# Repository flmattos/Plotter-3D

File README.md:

# Plotter-3D

#Engenharia da Computação

#PUCPR

#3D

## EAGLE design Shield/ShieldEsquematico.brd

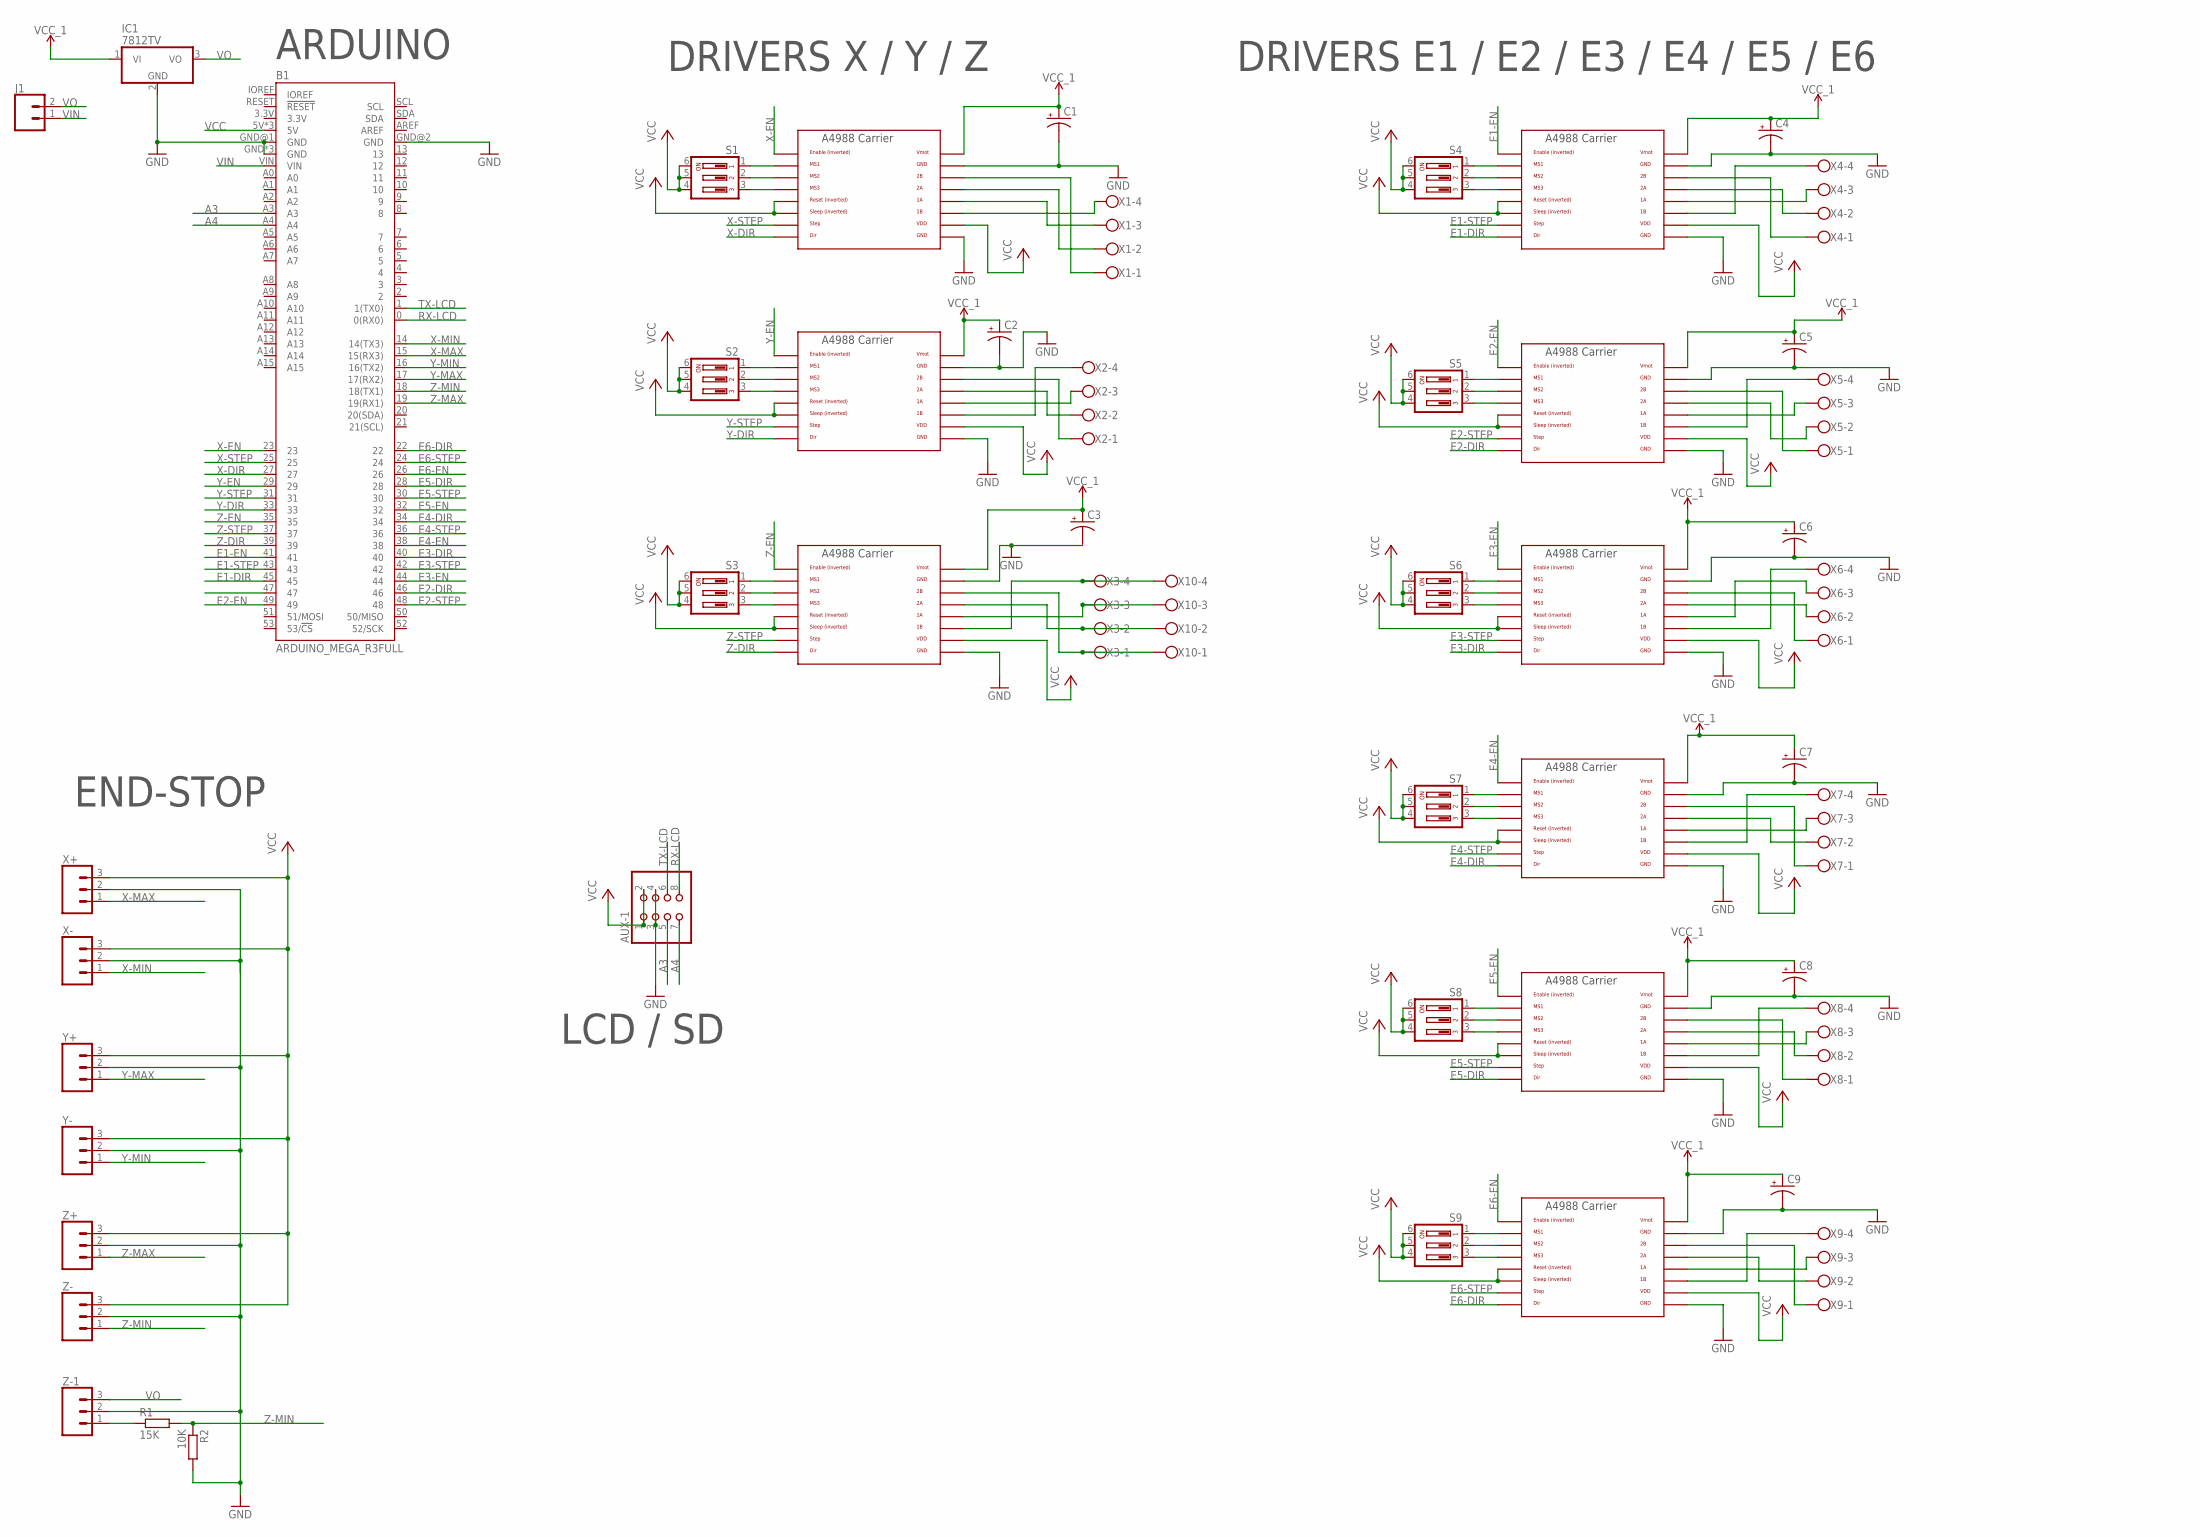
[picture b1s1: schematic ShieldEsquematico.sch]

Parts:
AUX-1: PINHD-2X4; 2X04
B1: ARDUINO_MEGA_R3FULL; ARDUINO_MEGA_NO_SILK
C1, C2, C3, C4, C5, C6, C7, C8, C9: CPOL-USE5-8.5; E5-8,5
IC1: 7812TV; TO220V
J1: CONN_02; 1X02
R1: 15K; 0207/10
R2: 10K; 0207/10
S1, S2, S3, S4, S5, S6, S7, S8, S9: DIP03YL
U$1, U$2, U$3, U$4, U$5, U$6, U$7, U$8, U$9: A4988BREAKOUT
X1, X2, X3, X4, X5, X6, X7, X8, X9, X10: W237-4
X+: CONN_03SCREW_LOCK; SCREWTERMINAL-3.5MM-3_LOCK.007S
X-: CONN_03SCREW_LOCK; SCREWTERMINAL-3.5MM-3_LOCK.007S
Y+: CONN_03SCREW_LOCK; SCREWTERMINAL-3.5MM-3_LOCK.007S
Y-: CONN_03SCREW_LOCK; SCREWTERMINAL-3.5MM-3_LOCK.007S
Z+: CONN_03SCREW_LOCK; SCREWTERMINAL-3.5MM-3_LOCK.007S
Z-, Z-1: CONN_03SCREW_LOCK; SCREWTERMINAL-3.5MM-3_LOCK.007S

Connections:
A3: AUX-1.5, B1.A3
A4: AUX-1.7, B1.A4
E1-DIR: B1.45, U$4.DIR
E1-EN: B1.41, U$4.EN
E1-STEP: B1.43, U$4.STEP
E2-DIR: B1.46, U$5.DIR
E2-EN: B1.49, U$5.EN
E2-STEP: B1.48, U$5.STEP
E3-DIR: B1.40, U$6.DIR
E3-EN: B1.44, U$6.EN
E3-STEP: B1.42, U$6.STEP
E4-DIR: B1.34, U$7.DIR
E4-EN: B1.38, U$7.EN
E4-STEP: B1.36, U$7.STEP
E5-DIR: B1.28, U$8.DIR
E5-EN: B1.32, U$8.EN
E5-STEP: B1.30, U$8.STEP
E6-DIR: B1.22, U$9.DIR
E6-EN: B1.26, U$9.EN
E6-STEP: B1.24, U$9.STEP
GND: AUX-1.3, AUX-1.4, B1.GND, B1.GND@1 (GND), B1.GND@2 (GND), B1.GND@3 (GND), B1.GND@4 (GND), C1.-, C2.-, C3.-, C4.-, C5.-, C6.-, C7.-, C8.-, C9.-, IC1.2 (GND), R2.2, U$1.GND, U$1.GND@0 (GND), U$2.GND, U$2.GND@0 (GND), U$3.GND, U$3.GND@0 (GND), U$4.GND, U$4.GND@0 (GND), U$5.GND, U$5.GND@0 (GND), U$6.GND, U$6.GND@0 (GND), U$7.GND, U$7.GND@0 (GND), U$8.GND, U$8.GND@0 (GND), U$9.GND, U$9.GND@0 (GND), X+.2, X-.2, Y+.2, Y-.2, Z+.2, Z-.2, Z-1.2
unnamed: S1.1, U$1.MS1
unnamed: S1.2, U$1.MS2
unnamed: S1.3, U$1.MS3
unnamed: U$1.1B, X1.4
unnamed: U$1.1A, X1.3
unnamed: U$1.2A, X1.2
unnamed: U$1.2B, X1.1
unnamed: S2.1, U$2.MS1
unnamed: S2.2, U$2.MS2
unnamed: S2.3, U$2.MS3
unnamed: U$2.1B, X2.4
unnamed: U$3.2B, X3.1, X10.1
unnamed: U$2.2A, X2.2
unnamed: U$2.2B, X2.1
unnamed: S3.1, U$3.MS1
unnamed: S3.2, U$3.MS2
unnamed: S3.3, U$3.MS3
unnamed: U$3.2A, X3.2, X10.2
unnamed: U$3.1A, X3.3, X10.3
unnamed: U$3.1B, X3.4, X10.4
unnamed: U$4.2B, X4.1
unnamed: S4.1, U$4.MS1
unnamed: S4.2, U$4.MS2
unnamed: S4.3, U$4.MS3
unnamed: U$4.2A, X4.2
unnamed: U$4.1A, X4.3
unnamed: U$4.1B, X4.4
unnamed: U$6.1A, X6.3
unnamed: S5.1, U$5.MS1
unnamed: S5.2, U$5.MS2
unnamed: S5.3, U$5.MS3
unnamed: U$5.2B, X5.1
unnamed: U$5.2A, X5.2
unnamed: U$5.1A, X5.3
unnamed: U$5.1B, X5.4
unnamed: S6.1, U$6.MS1
unnamed: S6.2, U$6.MS2
unnamed: S6.3, U$6.MS3
unnamed: U$6.1B, X6.4
unnamed: U$7.2A, X7.2
unnamed: U$6.2A, X6.2
unnamed: U$6.2B, X6.1
unnamed: S7.1, U$7.MS1
unnamed: S7.2, U$7.MS2
unnamed: S7.3, U$7.MS3
unnamed: U$7.1A, X7.3
unnamed: U$7.1B, X7.4
unnamed: U$9.2B, X9.1
unnamed: U$7.2B, X7.1
unnamed: S8.1, U$8.MS1
unnamed: S8.2, U$8.MS2
unnamed: S8.3, U$8.MS3
unnamed: U$8.2B, X8.1
unnamed: U$8.2A, X8.2
unnamed: U$8.1A, X8.3
unnamed: U$8.1B, X8.4
unnamed: S9.1, U$9.MS1
unnamed: S9.2, U$9.MS2
unnamed: S9.3, U$9.MS3
unnamed: U$9.2A, X9.2
unnamed: U$9.1A, X9.3
unnamed: U$9.1B, X9.4
unnamed: R1.1, Z-1.1
unnamed: U$2.1A, X2.3
RX-LCD: AUX-1.8, B1.0 (0(RX0))
TX-LCD: AUX-1.6, B1.1 (1(TX0))
VCC: AUX-1.1, AUX-1.2, B1.5V, B1.5V@1 (5V), B1.5V@2 (5V), S1.4, S1.5, S1.6, S2.4, S2.5, S2.6, S3.4, S3.5, S3.6, S4.4, S4.5, S4.6, S5.4, S5.5, S5.6, S6.4, S6.5, S6.6, S7.4, S7.5, S7.6, S8.4, S8.5, S8.6, S9.4, S9.5, S9.6, U$1.RST, U$1.SLP (SLEEP), U$1.VDD, U$2.RST, U$2.SLP (SLEEP), U$2.VDD, U$3.RST, U$3.SLP (SLEEP), U$3.VDD, U$4.RST, U$4.SLP (SLEEP), U$4.VDD, U$5.RST, U$5.SLP (SLEEP), U$5.VDD, U$6.RST, U$6.SLP (SLEEP), U$6.VDD, U$7.RST, U$7.SLP (SLEEP), U$7.VDD, U$8.RST, U$8.SLP (SLEEP), U$8.VDD, U$9.RST, U$9.SLP (SLEEP), U$9.VDD, X+.3, X-.3, Y+.3, Y-.3, Z+.3, Z-.3
VCC_1: C1.+, C2.+, C3.+, C4.+, C5.+, C6.+, C7.+, C8.+, C9.+, IC1.1 (VI), U$1.VMOT, U$2.VMOT, U$3.VMOT, U$4.VMOT, U$5.VMOT, U$6.VMOT, U$7.VMOT, U$8.VMOT, U$9.VMOT
VIN: B1.VIN, J1.1
VO: IC1.3 (VO), J1.2, Z-1.3
X-DIR: B1.27, U$1.DIR
X-EN: B1.23, U$1.EN
X-MAX: B1.15 (15(RX3)), X+.1
X-MIN: B1.14 (14(TX3)), X-.1
X-STEP: B1.25, U$1.STEP
Y-DIR: B1.33, U$2.DIR
Y-EN: B1.29, U$2.EN
Y-MAX: B1.17 (17(RX2)), Y+.1
Y-MIN: B1.16 (16(TX2)), Y-.1
Y-STEP: B1.31, U$2.STEP
Z-DIR: B1.39, U$3.DIR
Z-EN: B1.35, U$3.EN
Z-MAX: B1.19 (19(RX1)), Z+.1
Z-MIN: B1.18 (18(TX1)), R1.2, R2.1, Z-.1
Z-STEP: B1.37, U$3.STEP

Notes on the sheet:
END-STOP
LCD / SD
DRIVERS X / Y / Z
DRIVERS E1 / E2 / E3 / E4 / E5 / E6
ARDUINO

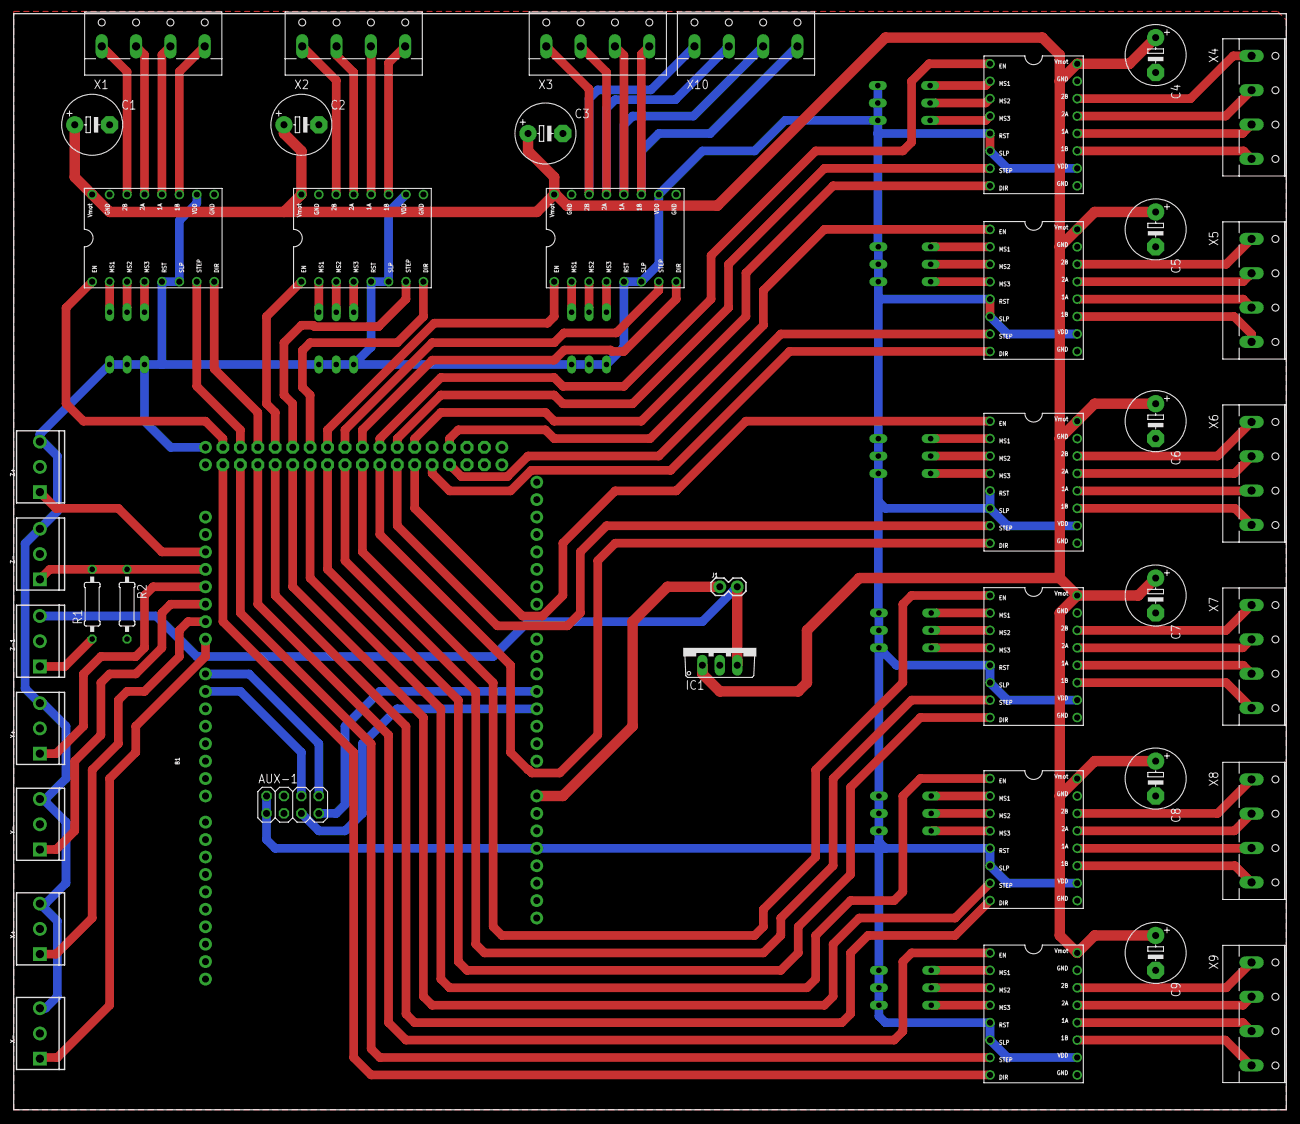
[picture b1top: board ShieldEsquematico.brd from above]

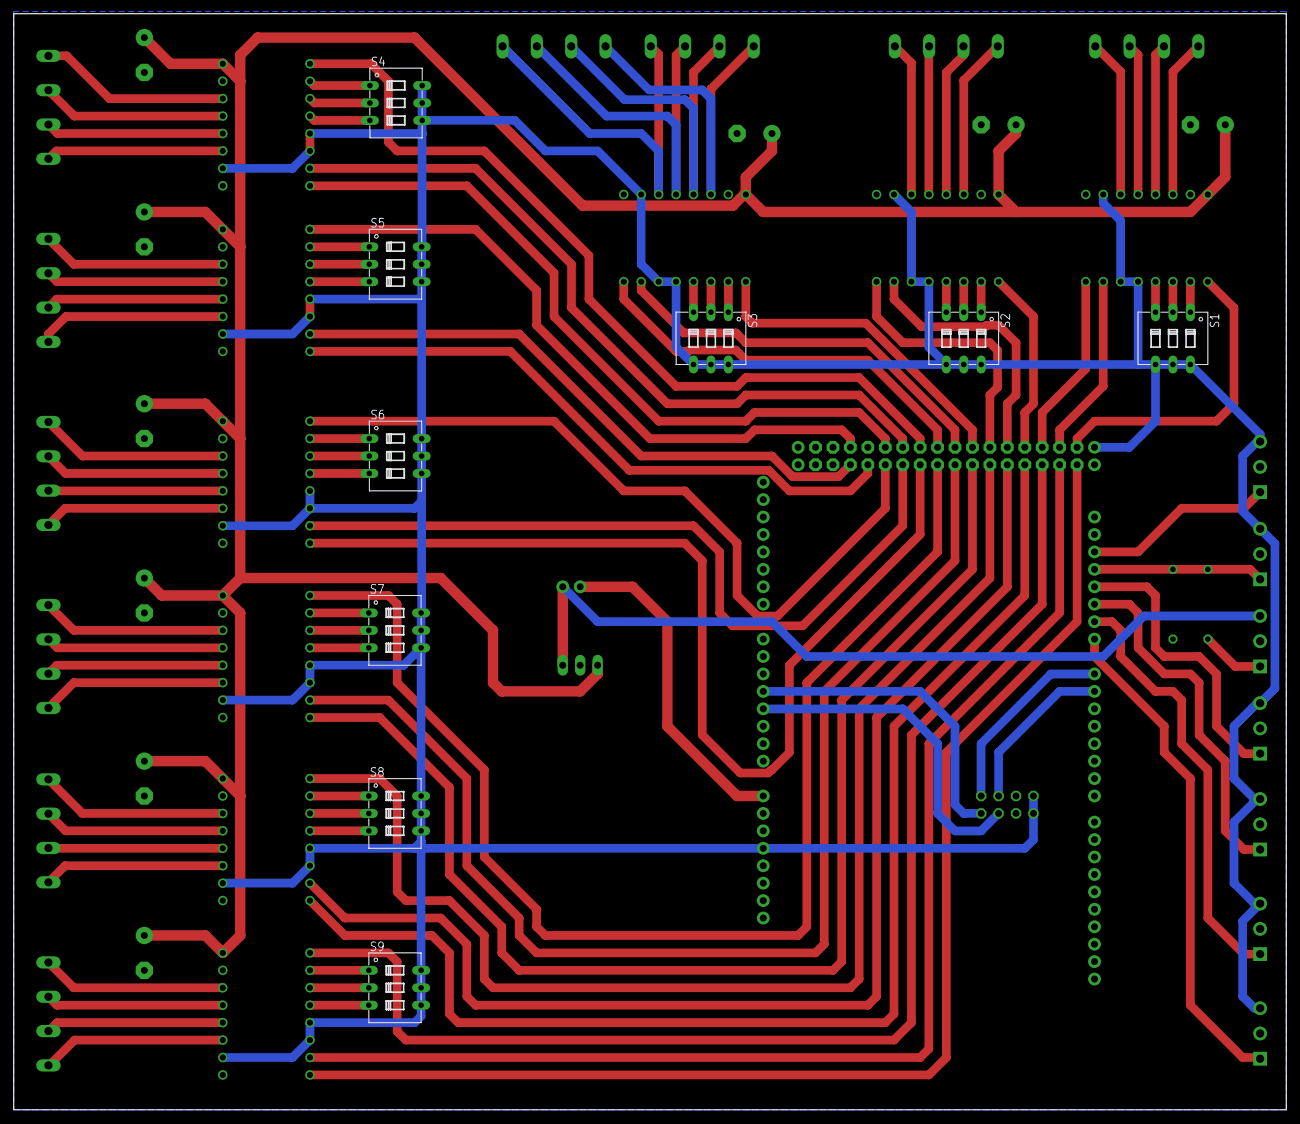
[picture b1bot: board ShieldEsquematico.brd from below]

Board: 2 copper layers, 185.4 x 159.7 mm, 50 parts (9 on the bottom side), 106 nets.

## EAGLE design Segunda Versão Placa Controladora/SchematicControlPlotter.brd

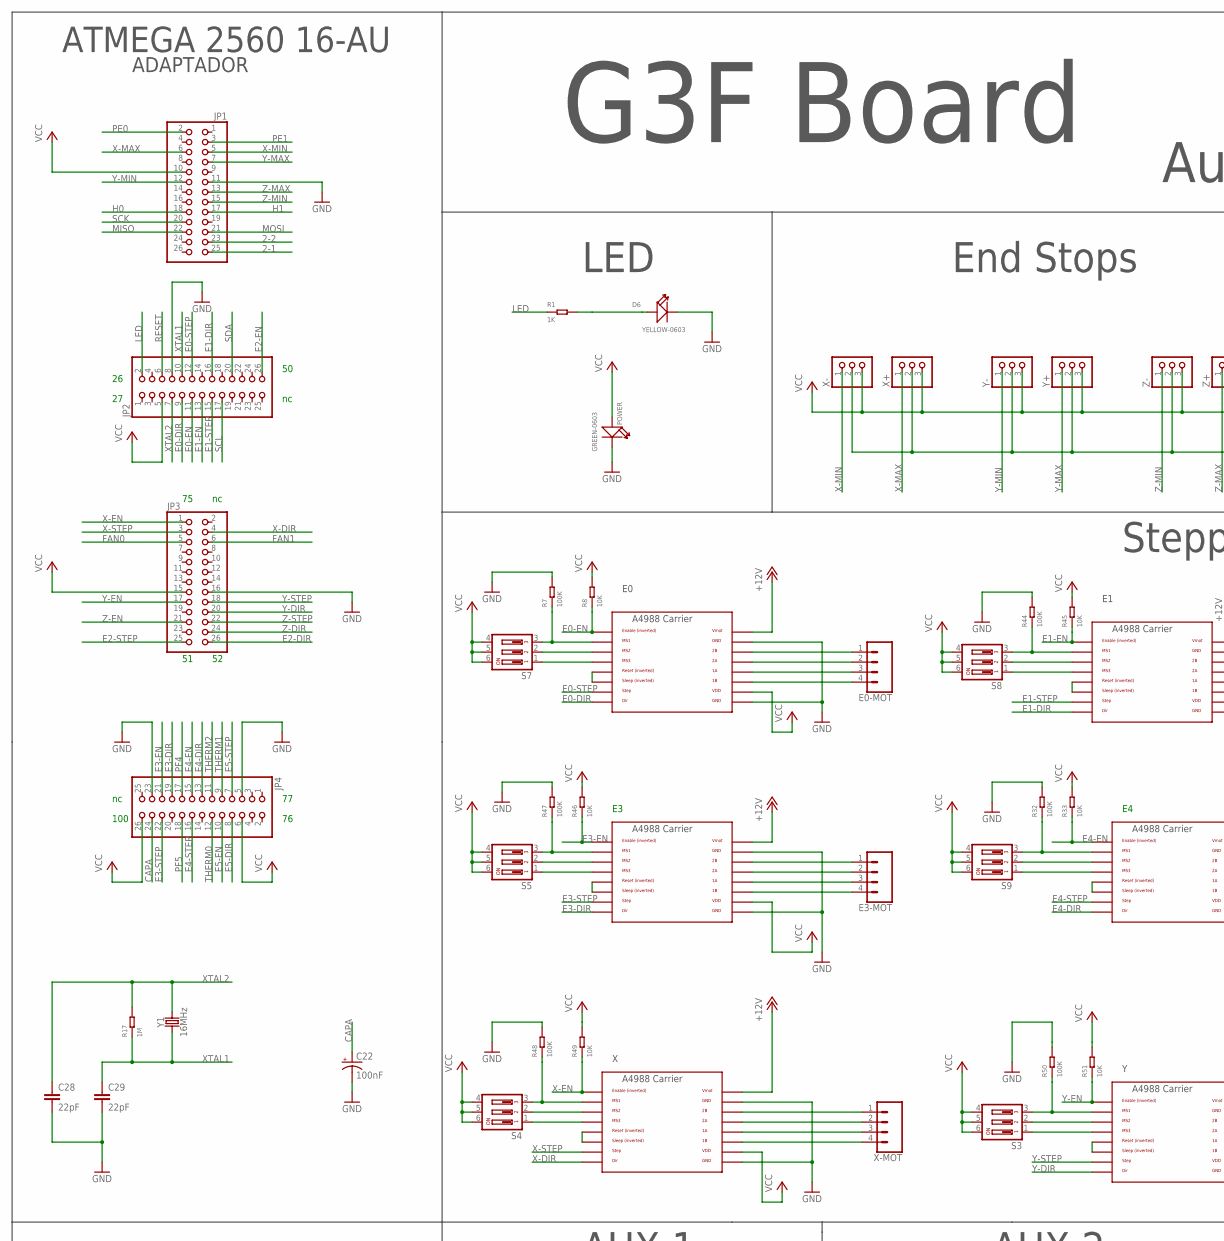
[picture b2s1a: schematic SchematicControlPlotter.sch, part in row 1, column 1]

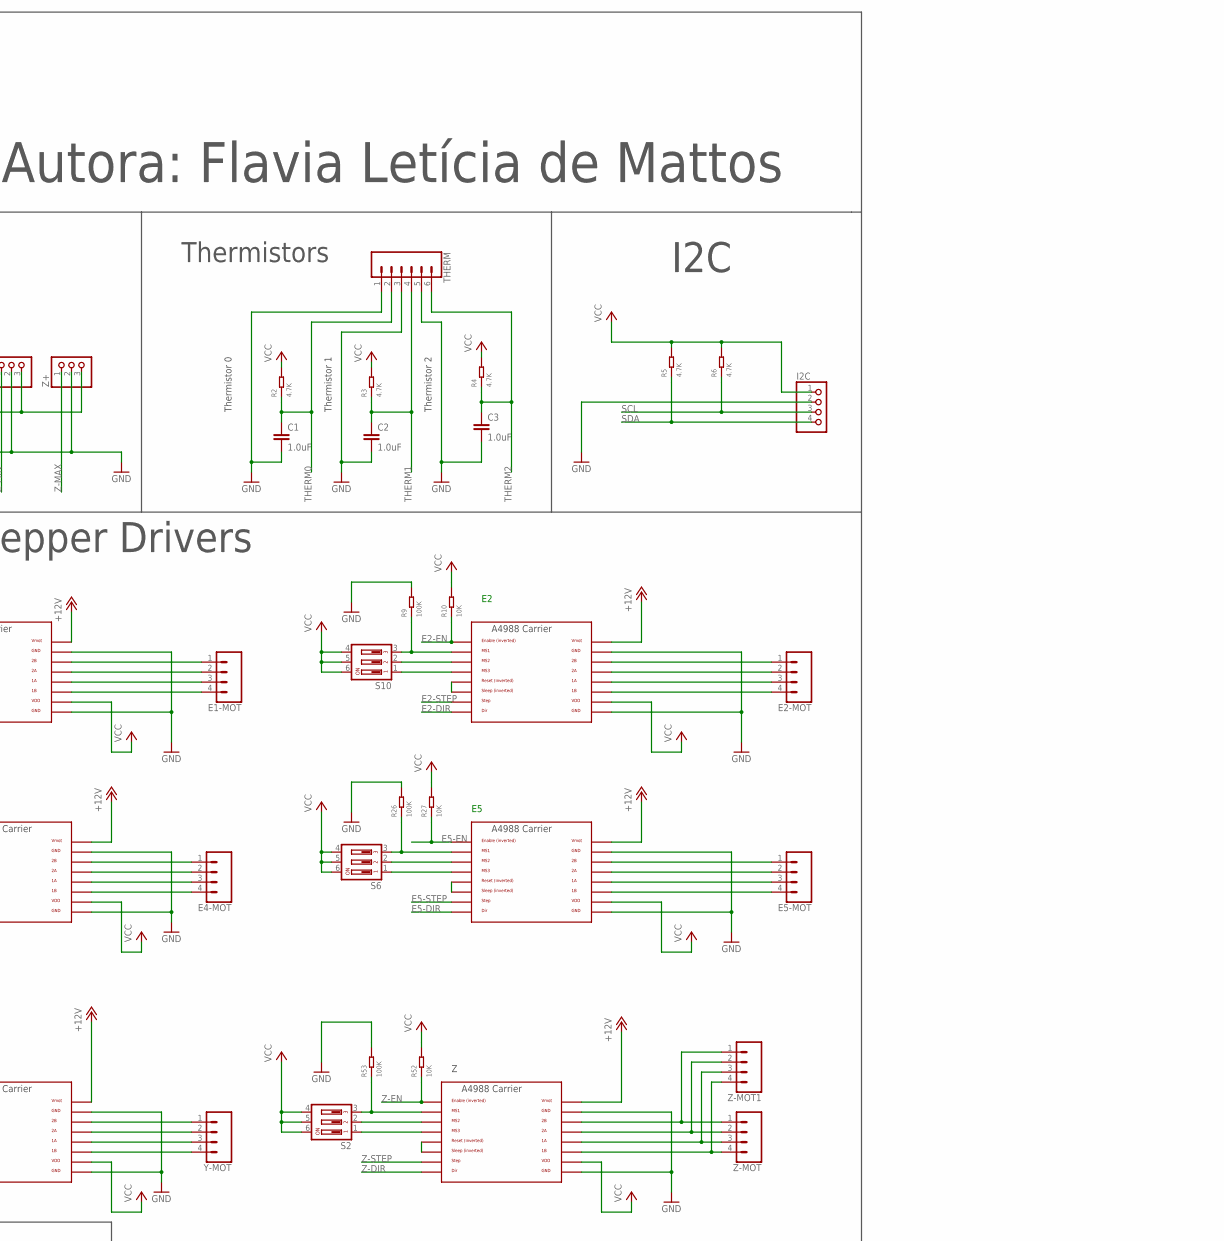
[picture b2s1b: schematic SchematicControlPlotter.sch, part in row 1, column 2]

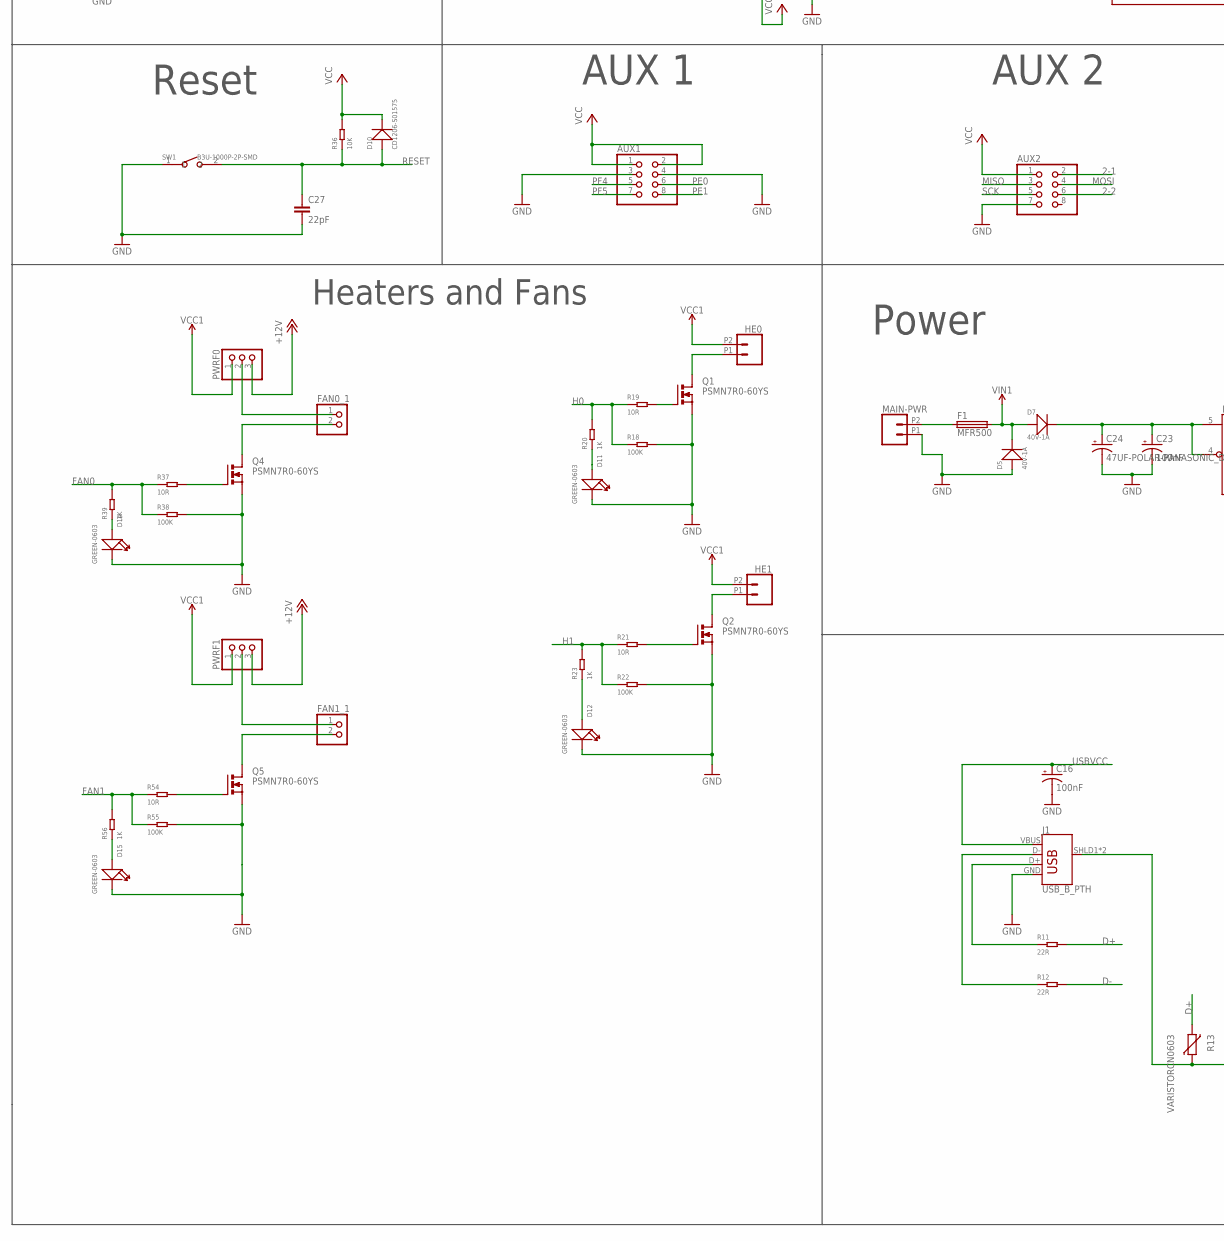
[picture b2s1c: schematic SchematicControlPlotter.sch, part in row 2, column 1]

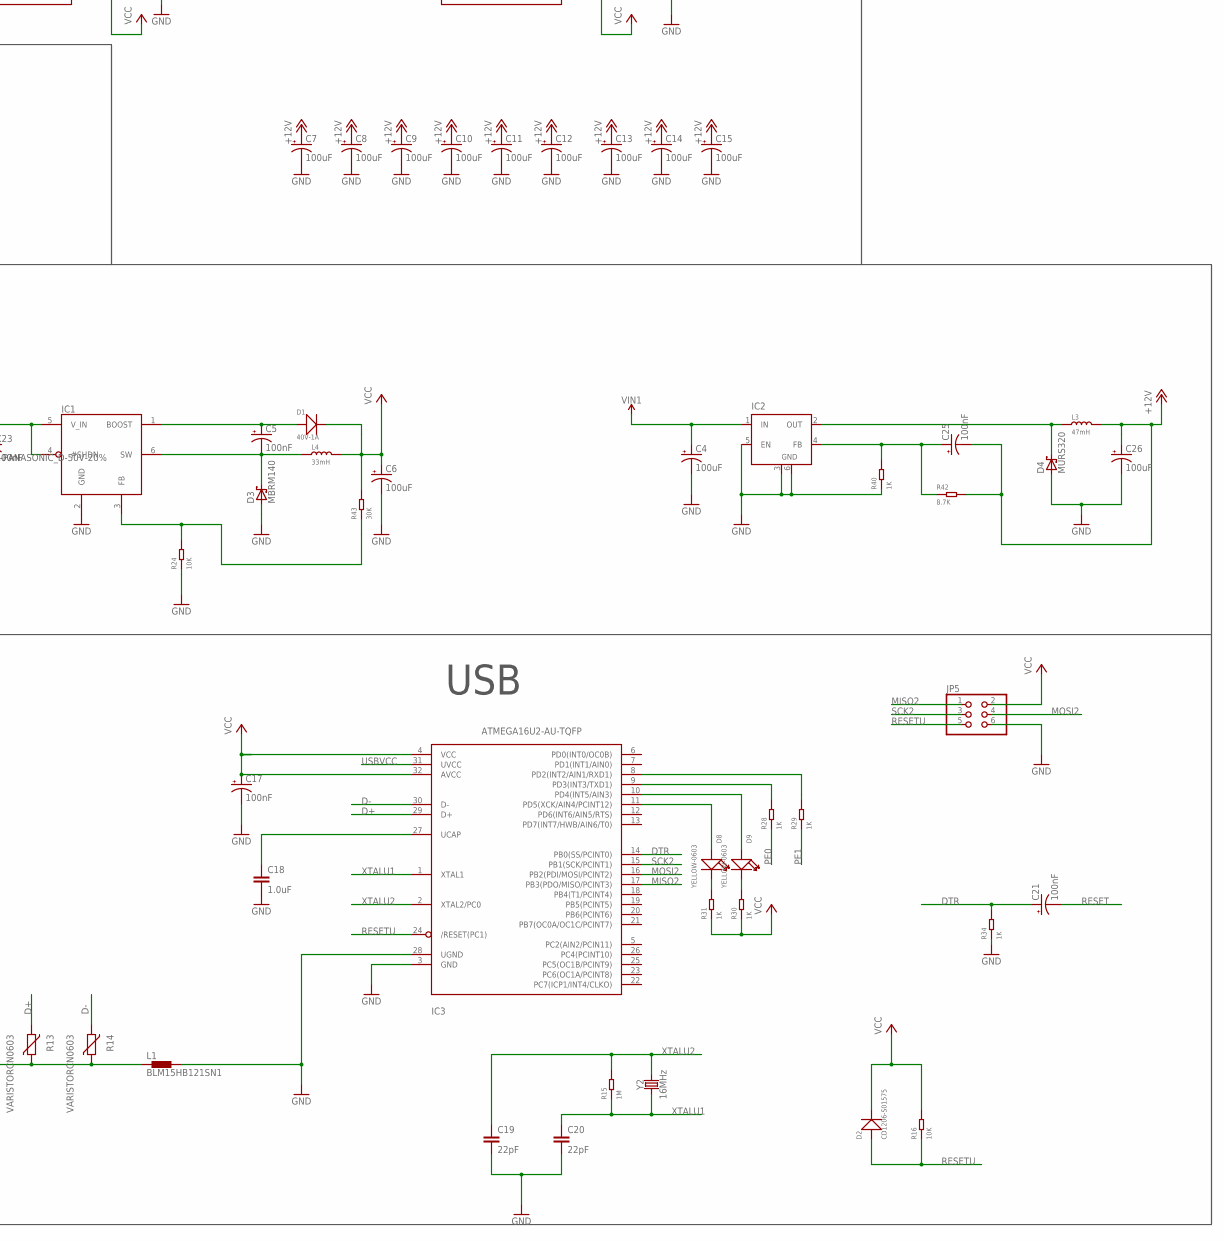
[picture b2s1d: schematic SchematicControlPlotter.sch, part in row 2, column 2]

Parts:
AUX1, AUX2: PINHD-2X4; 2X04
C1, C2, C3: 1.0uF; 0805
C4, C6, C26: 100uF; NIC_10X10.5_CAP
C5, C25: 100nF; NIC_10X10.5_CAP
C7, C8, C9, C10, C11, C12, C13, C14, C15: 100uF; PANASONIC_D
C16, C17, C21, C22, C23: 100nF; PANASONIC_G
C18: 1.0uF; 0603
C19, C20, C27, C28, C29: 22pF; 0603
C24: 47UF-POLAR-PANASONIC_D-50V-20%; PANASONIC_D
D1, D5, D7: 40V-1A; DO-214AC
D2, D10: CD1206-S01575; DO-214AC
D3: MBRM140; SMB
D4: MURS320; SMB
D6, D8, D9: YELLOW-0603; LED-0603
D11, D12, D14, D15: GREEN-0603; LED-0603
E0-MOT, E1-MOT, E2-MOT, E3-MOT, E4-MOT, E5-MOT: CONN_04SCREW_LOCK; SCREWTERMINAL-3.5MM-4_LOCK
F1: MFR500; LITTLEFUSE
FAN0_1, FAN1_1: PINHD-1X2; 1X02
HE0, HE1: CONN_022.54MM_SCREWTERM; 1X02_2.54_SCREWTERM
I2C: PINHD-1X4; 1X04
IC1: LT1933ES6; SOT23-6
IC2: LM2596S; TO263-5
IC3: ATMEGA16U2-AU-TQFP; TQFP32-08
J1: USB_B_PTH; USB-B-PTH
JP1, JP2, JP3, JP4: PINHD-2X13; 2X13
JP5: PINHD-2X3; 2X03
L1: BLM15HB121SN1; 0402
L3: 47mH; L0402
L4: 33mH; L0402
MAIN-PWR: CONN_022.54MM_SCREWTERM; 1X02_2.54_SCREWTERM
POWER: GREEN-0603; LED-0603
PWRF0, PWRF1: PINHD-1X3; 1X03
Q1, Q2, Q4, Q5: PSMN7R0-60YS; TO220BH
R1, R20, R23, R28, R29, R30, R31, R34, R39, R56: 1K; R0603
R2, R3, R4, R5, R6: 4.7K; R0603
R7, R9, R18, R22, R26, R32, R38, R44, R47, R48, R50, R53, R55: 100K; R0603
R8, R10, R16, R24, R27, R33, R36, R45, R46, R49, R51, R52: 10K; R0603
R11, R12: 22R; R0603
R13, R14: VARISTORCN0603; CT/CN0603
R15, R17: 1M; R0603
R19, R21, R37, R54: 10R; R0603
R40: 1K; R0805
R42: 8.7K; R0805
R43: 30K; R0603
S2, S3, S4, S5, S6, S7, S8, S9, S10: DP03; DP-03
SW1: B3U-1000P-2P-SMD; SW2-2.6-3.0X2.5X1.2+0.4MM
THERM: CONN_063.5MM-6; SCREWTERMINAL-3.5MM-6
U$1, U$2, U$4, U$5, U$7, U$8, U$9, U$10: A4988BREAKOUT
X: A4988BREAKOUT
X+: PINHD-1X3; 1X03
X-: PINHD-1X3; 1X03
X-MOT: CONN_04SCREW_LOCK; SCREWTERMINAL-3.5MM-4_LOCK
Y1, Y2: 16MHz; HC49US
Y+: PINHD-1X3; 1X03
Y-: PINHD-1X3; 1X03
Y-MOT: CONN_04SCREW_LOCK; SCREWTERMINAL-3.5MM-4_LOCK
Z+: PINHD-1X3; 1X03
Z-: PINHD-1X3; 1X03
Z-MOT, Z-MOT1: CONN_04SCREW_LOCK; SCREWTERMINAL-3.5MM-4_LOCK

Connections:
2-1: AUX2.2, JP1.25
2-2: AUX2.6, JP1.23
+12V: C7.+, C8.+, C9.+, C10.+, C11.+, C12.+, C13.+, C14.+, C15.+, C25.-, C26.+, L3.2, PWRF0.3, PWRF1.3, R42.2, U$1.VMOT, U$2.VMOT, U$4.VMOT, U$5.VMOT, U$7.VMOT, U$8.VMOT, U$9.VMOT, U$10.VMOT, X.VMOT
CAPA: C22.+, JP4.24
D+: IC3.29 (D+), R11.2, R13.2
D-: IC3.30 (D-), R12.2, R14.2
DTR: C21.+, IC3.14 (PB0(SS/PCINT0)), R34.2
E0-DIR: JP2.9, U$1.DIR
E0-EN: JP2.11, R8.1, U$1.EN
E0-STEP: JP2.12, U$1.STEP
E1-DIR: JP2.16, U$2.DIR
E1-EN: JP2.13, R45.1, U$2.EN
E1-STEP: JP2.15, U$2.STEP
E2-DIR: JP3.26, U$7.DIR
E2-EN: JP2.26, R10.1, U$7.EN
E2-STEP: JP3.25, U$7.STEP
E3-DIR: JP4.19, U$8.DIR
E3-EN: JP4.21, R46.1, U$8.EN
E3-STEP: JP4.22, U$8.STEP
E4-DIR: JP4.13, U$9.DIR
E4-EN: JP4.15, R33.1, U$9.EN
E4-STEP: JP4.16, U$9.STEP
E5-DIR: JP4.8, U$10.DIR
E5-EN: JP4.10, R27.1, U$10.EN
E5-STEP: JP4.7, U$10.STEP
FAN0: JP3.5, R37.1, R38.1, R39.2
FAN1: JP3.6, R54.1, R55.1, R56.2
GND: AUX1.3, AUX1.4, AUX2.7, C1.2, C2.2, C3.2, C4.-, C6.-, C7.-, C8.-, C9.-, C10.-, C11.-, C12.-, C13.-, C14.-, C15.-, C16.-, C17.-, C18.2, C19.2, C20.2, C22.-, C23.-, C24.-, C26.-, C27.2, C28.2, C29.2, D3.A, D4.A, D5.1 (+), D6.-, D11.-, D12.-, D14.-, D15.-, I2C.2, IC1.2 (GND), IC2.3 (GND), IC2.5 (EN), IC2.6 (GND), IC3.3 (GND), IC3.28 (UGND), J1.GND, JP1.11, JP2.8, JP3.16, JP4.5, JP4.23, JP5.6, L1.2, MAIN-PWR.P1 (1), POWER.-, Q1.S, Q2.S, Q4.S, Q5.S, R7.2, R9.2, R18.2, R22.2, R24.1, R26.2, R32.2, R34.1, R38.2, R40.1, R44.2, R47.2, R48.2, R50.2, R53.2, R55.2, SW1.1, THERM.1, THERM.3, THERM.5, U$1.GND, U$1.GND@0 (GND), U$2.GND, U$2.GND@0 (GND), U$4.GND, U$4.GND@0 (GND), U$5.GND, U$5.GND@0 (GND), U$7.GND, U$7.GND@0 (GND), U$8.GND, U$8.GND@0 (GND), U$9.GND, U$9.GND@0 (GND), U$10.GND, U$10.GND@0 (GND), X.GND, X.GND@0 (GND), X+.2, X-.2, Y+.2, Y-.2, Z+.2, Z-.2
H0: JP1.18, R18.1, R19.1, R20.2
H1: JP1.17, R21.1, R22.1, R23.2
LED: JP2.2, R1.1
MISO: AUX2.3, JP1.22
MISO2: IC3.17 (PB3(PDO/MISO/PCINT3)), JP5.1
MOSI: AUX2.4, JP1.21
MOSI2: IC3.16 (PB2(PDI/MOSI/PCINT2)), JP5.4
unnamed: D6.+, R1.2
unnamed: R7.1, S7.3, U$1.MS1
unnamed: R44.1, S8.3, U$2.MS1
unnamed: S7.2, U$1.MS2
unnamed: E0-MOT.1, U$1.2B
unnamed: E0-MOT.2, U$1.2A
unnamed: U$1.RST, U$1.SLP (SLEEP)
unnamed: E0-MOT.3, U$1.1A
unnamed: E0-MOT.4, U$1.1B
unnamed: S8.2, U$2.MS2
unnamed: S8.1, U$2.MS3
unnamed: R47.1, S5.3, U$8.MS1
unnamed: E1-MOT.1, U$2.2B
unnamed: E1-MOT.2, U$2.2A
unnamed: U$2.RST, U$2.SLP (SLEEP)
unnamed: E1-MOT.3, U$2.1A
unnamed: E1-MOT.4, U$2.1B
unnamed: R48.1, S4.3, X.MS1
unnamed: S4.2, X.MS2
unnamed: HE0.P1 (1), Q1.D
unnamed: X.2B, X-MOT.1
unnamed: X.2A, X-MOT.2
unnamed: X.1A, X-MOT.3
unnamed: X.1B, X-MOT.4
unnamed: R53.1, S2.3, U$5.MS1
unnamed: R50.1, S3.3, U$4.MS1
unnamed: S3.2, U$4.MS2
unnamed: S3.1, U$4.MS3
unnamed: S4.1, X.MS3
unnamed: R9.1, S10.3, U$7.MS1
unnamed: S2.2, U$5.MS2
unnamed: U$4.2B, Y-MOT.1
unnamed: U$4.2A, Y-MOT.2
unnamed: U$4.1A, Y-MOT.3
unnamed: U$4.1B, Y-MOT.4
unnamed: U$4.RST, U$4.SLP (SLEEP)
unnamed: S7.1, U$1.MS3
unnamed: Q1.G, R19.2
unnamed: S10.2, U$7.MS2
unnamed: U$5.RST, U$5.SLP (SLEEP)
unnamed: X.RST, X.SLP (SLEEP)
unnamed: S5.2, U$8.MS2
unnamed: U$5.2A, Z-MOT.2, Z-MOT1.2
unnamed: U$5.1A, Z-MOT.3, Z-MOT1.3
unnamed: U$5.1B, Z-MOT.4, Z-MOT1.4
unnamed: S10.1, U$7.MS3
unnamed: HE1.P1 (1), Q2.D
unnamed: D11.+, R20.1
unnamed: FAN0_1.1, PWRF0.2
unnamed: E3-MOT.1, U$8.2B
unnamed: Q2.G, R21.2
unnamed: D12.+, R23.1
unnamed: E2-MOT.1, U$7.2B
unnamed: S5.1, U$8.MS3
unnamed: E2-MOT.2, U$7.2A
unnamed: E2-MOT.3, U$7.1A
unnamed: E2-MOT.4, U$7.1B
unnamed: E3-MOT.2, U$8.2A
unnamed: U$7.RST, U$7.SLP (SLEEP)
unnamed: E3-MOT.3, U$8.1A
unnamed: E3-MOT.4, U$8.1B
unnamed: R26.1, S6.3, U$10.MS1
unnamed: S2.1, U$5.MS3
unnamed: S6.2, U$10.MS2
unnamed: U$8.RST, U$8.SLP (SLEEP)
unnamed: U$9.RST, U$9.SLP (SLEEP)
unnamed: R32.1, S9.3, U$9.MS1
unnamed: S9.2, U$9.MS2
unnamed: S9.1, U$9.MS3
unnamed: E4-MOT.1, U$9.2B
unnamed: E4-MOT.2, U$9.2A
unnamed: E4-MOT.3, U$9.1A
unnamed: E4-MOT.4, U$9.1B
unnamed: E5-MOT.1, U$10.2B
unnamed: E5-MOT.2, U$10.2A
unnamed: E5-MOT.3, U$10.1A
unnamed: E5-MOT.4, U$10.1B
unnamed: F1.1, MAIN-PWR.P2 (2)
unnamed: S6.1, U$10.MS3
unnamed: D4.C, IC2.2 (OUT), L3.1
unnamed: J1.D-, R12.1
unnamed: U$10.RST, U$10.SLP (SLEEP)
unnamed: J1.D+, R11.1
unnamed: J1.SHLD1 (SHIELD), J1.SHLD2 (SHIELD), L1.1, R13.1, R14.1
unnamed: IC3.8 (PD2(INT2/AIN1/RXD1)), R29.2
unnamed: C23.+, C24.+, D7.2 (-), IC1.4 (#SHDN), IC1.5 (V_IN)
unnamed: FAN1_1.1, PWRF1.2
unnamed: FAN1_1.2, Q5.D
unnamed: C25.+, IC2.4 (FB), R40.2, R42.1
unnamed: U$5.2B, Z-MOT.1, Z-MOT1.1
unnamed: C5.+, D1.1 (+), IC1.1 (BOOST)
unnamed: C5.-, D3.C, IC1.6 (SW), L4.1
unnamed: IC3.9 (PD3(INT3/TXD1)), R28.2
unnamed: FAN0_1.2, Q4.D
unnamed: C18.1, IC3.27 (UCAP)
unnamed: D9.+, IC3.10 (PD4(INT5/AIN3))
unnamed: IC1.3 (FB), R24.2, R43.1
unnamed: D8.+, IC3.11 (PD5(XCK/AIN4/PCINT12))
unnamed: D8.-, R31.2
unnamed: D9.-, R30.2
unnamed: Q4.G, R37.2
unnamed: Q5.G, R54.2
unnamed: D14.+, R39.1
unnamed: D15.+, R56.1
PE0: AUX1.6, JP1.2, R28.1
PE1: AUX1.8, JP1.3, R29.1
PF4: AUX1.5, JP4.17
PF5: AUX1.7, JP4.18
RESET: C21.-, C27.1, D10.1 (+), JP2.6, R36.1, SW1.2
RESETU: D2.1 (+), IC3.24 (/RESET(PC1)), JP5.5, R16.1
SCK: AUX2.5, JP1.20
SCK2: IC3.15 (PB1(SCK/PCINT1)), JP5.3
SCL: I2C.3, JP2.17, R6.1
SDA: I2C.4, JP2.20, R5.1
THERM0: C1.1, JP4.12, R2.1, THERM.2
THERM1: C2.1, JP4.9, R3.1, THERM.4
THERM2: C3.1, JP4.11, R4.1, THERM.6
USBVCC: C16.+, IC3.31 (UVCC), J1.VBUS
VCC: AUX1.1, AUX1.2, AUX2.1, C4.+, C6.+, C17.+, D1.2 (-), D2.2 (-), D5.2 (-), D7.1 (+), D10.2 (-), F1.2, I2C.1, IC2.1 (IN), IC3.4 (VCC), IC3.32 (AVCC), JP1.10, JP2.5, JP3.15, JP4.6, JP4.26, JP5.2, L4.2, POWER.+, R2.2, R3.2, R4.2, R5.2, R6.2, R8.2, R10.2, R16.2, R27.2, R30.1, R31.1, R33.2, R36.2, R43.2, R45.2, R46.2, R49.2, R51.2, R52.2, S2.4, S2.5, S2.6, S3.4, S3.5, S3.6, S4.4, S4.5, S4.6, S5.4, S5.5, S5.6, S6.4, S6.5, S6.6, S7.4, S7.5, S7.6, S8.4, S8.5, S8.6, S9.4, S9.5, S9.6, S10.4, S10.5, S10.6, U$1.VDD, U$2.VDD, U$4.VDD, U$5.VDD, U$7.VDD, U$8.VDD, U$9.VDD, U$10.VDD, X.VDD, X+.3, X-.3, Y+.3, Y-.3, Z+.3, Z-.3
VCC_1: HE0.P2 (2), HE1.P2 (2), PWRF0.1, PWRF1.1
X-DIR: JP3.4, X.DIR
X-EN: JP3.1, R49.1, X.EN
X-MAX: JP1.6, X+.1
X-MIN: JP1.5, X-.1
X-STEP: JP3.3, X.STEP
XTAL1: C29.1, JP2.10, R17.1, Y1.1
XTAL2: C28.1, JP2.7, R17.2, Y1.2
XTALU1: C20.1, IC3.1 (XTAL1), R15.1, Y2.1
XTALU2: C19.1, IC3.2 (XTAL2/PC0), R15.2, Y2.2
Y-DIR: JP3.20, U$4.DIR
Y-EN: JP3.17, R51.1, U$4.EN
Y-MAX: JP1.7, Y+.1
Y-MIN: JP1.12, Y-.1
Y-STEP: JP3.18, U$4.STEP
Z-DIR: JP3.24, U$5.DIR
Z-EN: JP3.21, R52.1, U$5.EN
Z-MAX: JP1.13, Z+.1
Z-MIN: JP1.15, Z-.1
Z-STEP: JP3.22, U$5.STEP

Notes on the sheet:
ATMEGA 2560 16-AU
LED
G3F Board
End Stops
Thermistors
Thermistor 0
Thermistor 1
Thermistor 2
I2C
Stepper Drivers
Reset
AUX 1
AUX 2
Power
USB
Autora: Flavia Letícia de Mattos
ADAPTADOR
100
Heaters and Fans

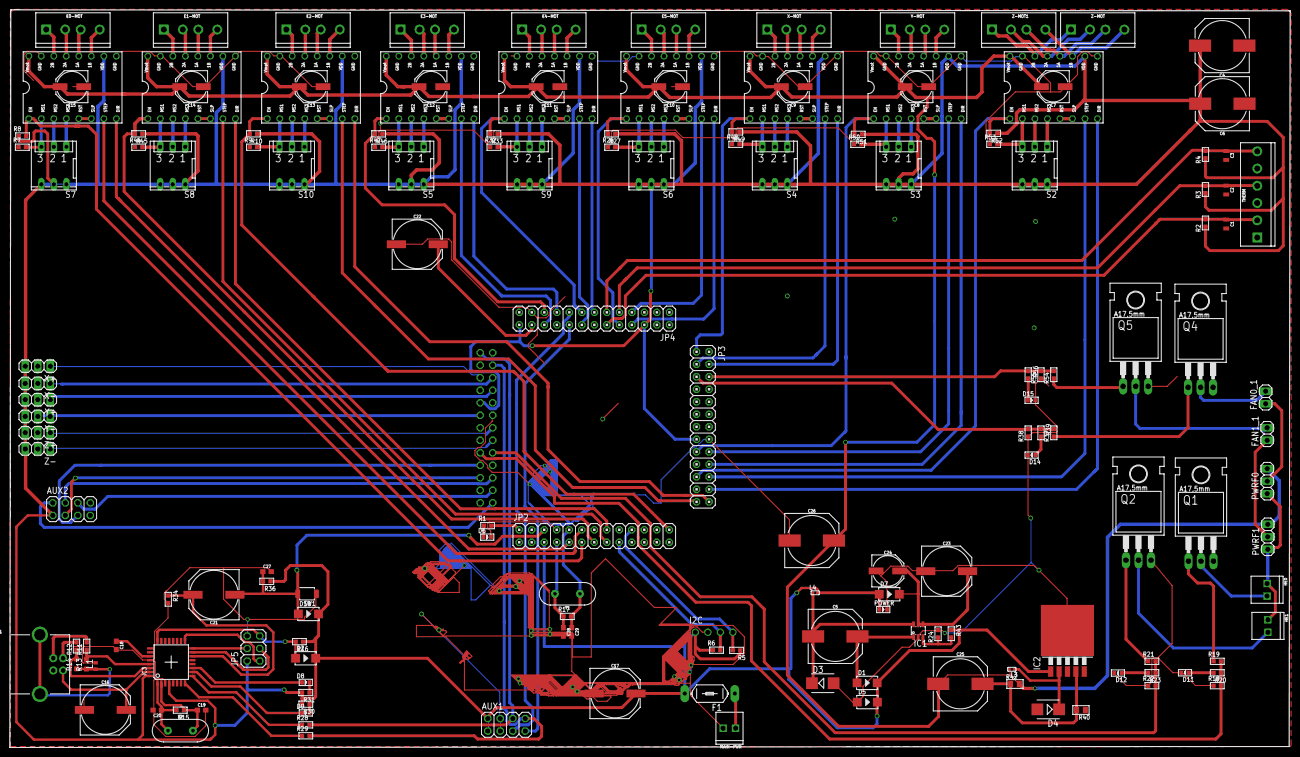
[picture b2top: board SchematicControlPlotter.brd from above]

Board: 2 copper layers, 260.0 x 149.8 mm, 162 parts (1 on the bottom side), 174 nets.

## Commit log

2018-07-24 PrimeiraAtualização
2018-10-13 Atualização Periodica
    Separação das Pastas. Renomear pastas.
2018-10-17 Atualizacao Periodica

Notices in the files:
parts and their libraries:
SparkFun-Connectors: Licensing: Creative Commons ShareAlike 4.0 International - https://creativecommons.org/licenses/by-sa/4.0
